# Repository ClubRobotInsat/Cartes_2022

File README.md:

# Cartes 2022
Toutes les cartes électroniques du Club pour l'année 2022 réalisées sur KiCAD. 

Liste des cartes dans ce répértoire:

|ID  | Description | 
|----|-------------|
|AAA | Carte de prototypage petite pour CAN Transreceiver MCP2551  | 
|AAB | Carte de prototypage grande pour CAN Transreceiver MCP2551  | 
|BAA | Carte du module de base pour toutes les STM32 v1            |
|BAC | Carte Alimentation 12V et 5V	                           |

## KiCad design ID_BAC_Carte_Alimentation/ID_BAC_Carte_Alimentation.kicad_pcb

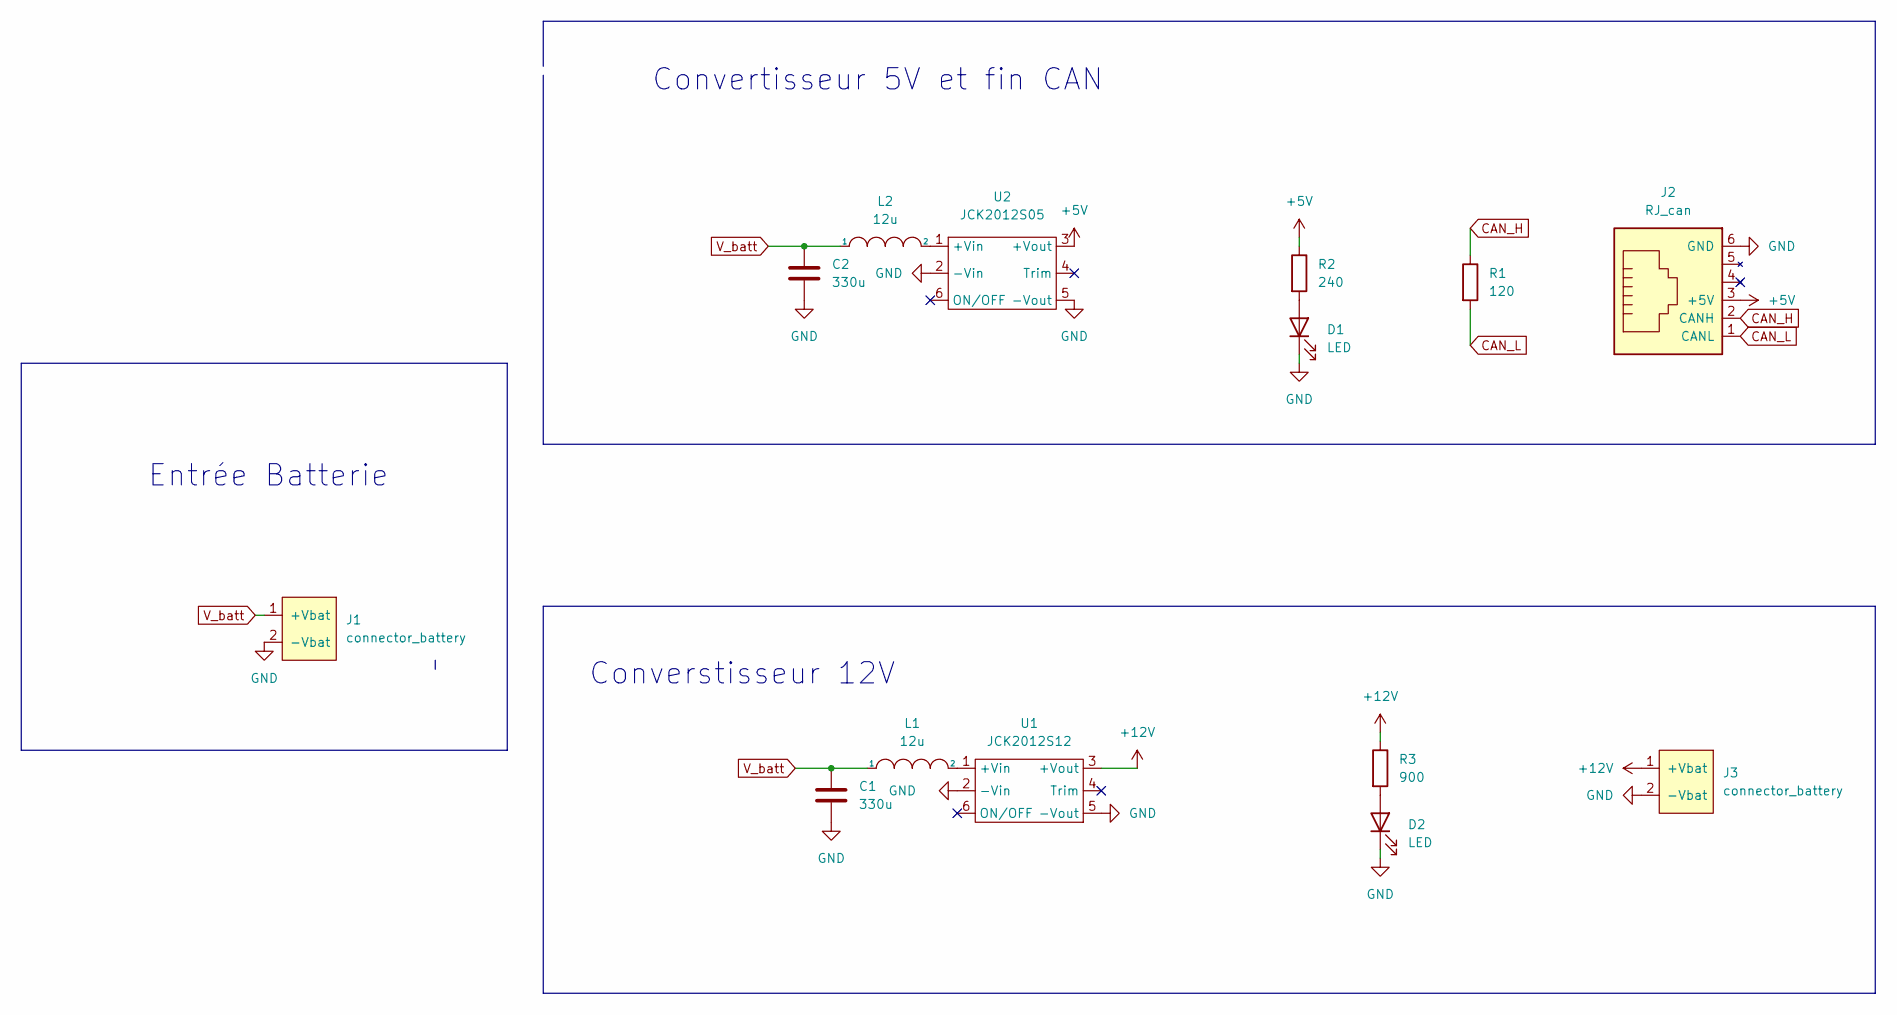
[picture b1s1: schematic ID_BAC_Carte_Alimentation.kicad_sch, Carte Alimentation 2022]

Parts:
C1, C2: 330u; CP_Radial_D7.5mm_P2.50mm
D1, D2: LED; LED_D5.0mm
J1, J3: connector_battery; WR_TBL_3137_2pins
J2: RJ_can; RJ12
L1, L2: 12u; L_Radial_D7.8mm_P5.00mm_Fastron_07HCP
R1: 120; R_0805_2012Metric_Pad1.20x1.40mm_HandSolder
R2: 240; R_0805_2012Metric_Pad1.20x1.40mm_HandSolder
R3: 900; R_0805_2012Metric_Pad1.20x1.40mm_HandSolder
U1: JCK2012S12; JCK2012S05
U2: JCK2012S05

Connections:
+5V: J2.3 (+5V), R2.1, U2.3 (+Vout)
+12V: J3.1 (+Vbat), R3.1, U1.3 (+Vout)
CAN_H: J2.2 (CANH), R1.1
CAN_L: J2.1 (CANL), R1.2
GND: C1.2, C2.2, D1.1 (K), D2.1 (K), J1.2 (-Vbat), J2.6 (GND), J3.2 (-Vbat), U1.2 (-Vin), U1.5 (-Vout), U2.2 (-Vin), U2.5 (-Vout)
unnamed: D1.2 (A), R2.2
unnamed: D2.2 (A), R3.2
unnamed: L1.2, U1.1 (+Vin)
unnamed: L2.2, U2.1 (+Vin)
V_batt: C1.1, C2.1, J1.1 (+Vbat), L1.1, L2.1

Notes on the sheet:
Entrée Batterie
Convertisseur 5V et fin CAN
Converstisseur 12V

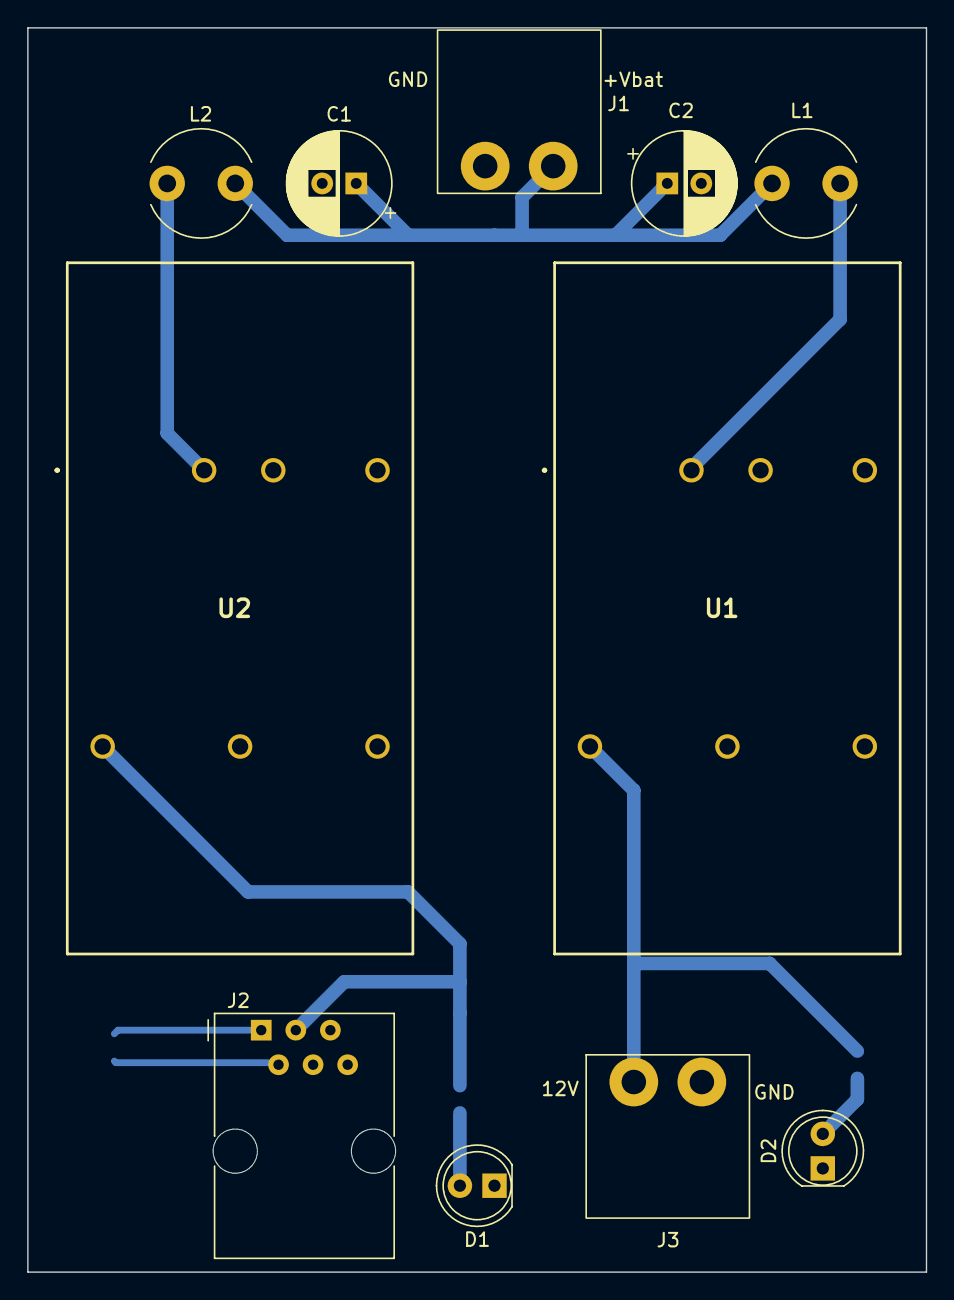
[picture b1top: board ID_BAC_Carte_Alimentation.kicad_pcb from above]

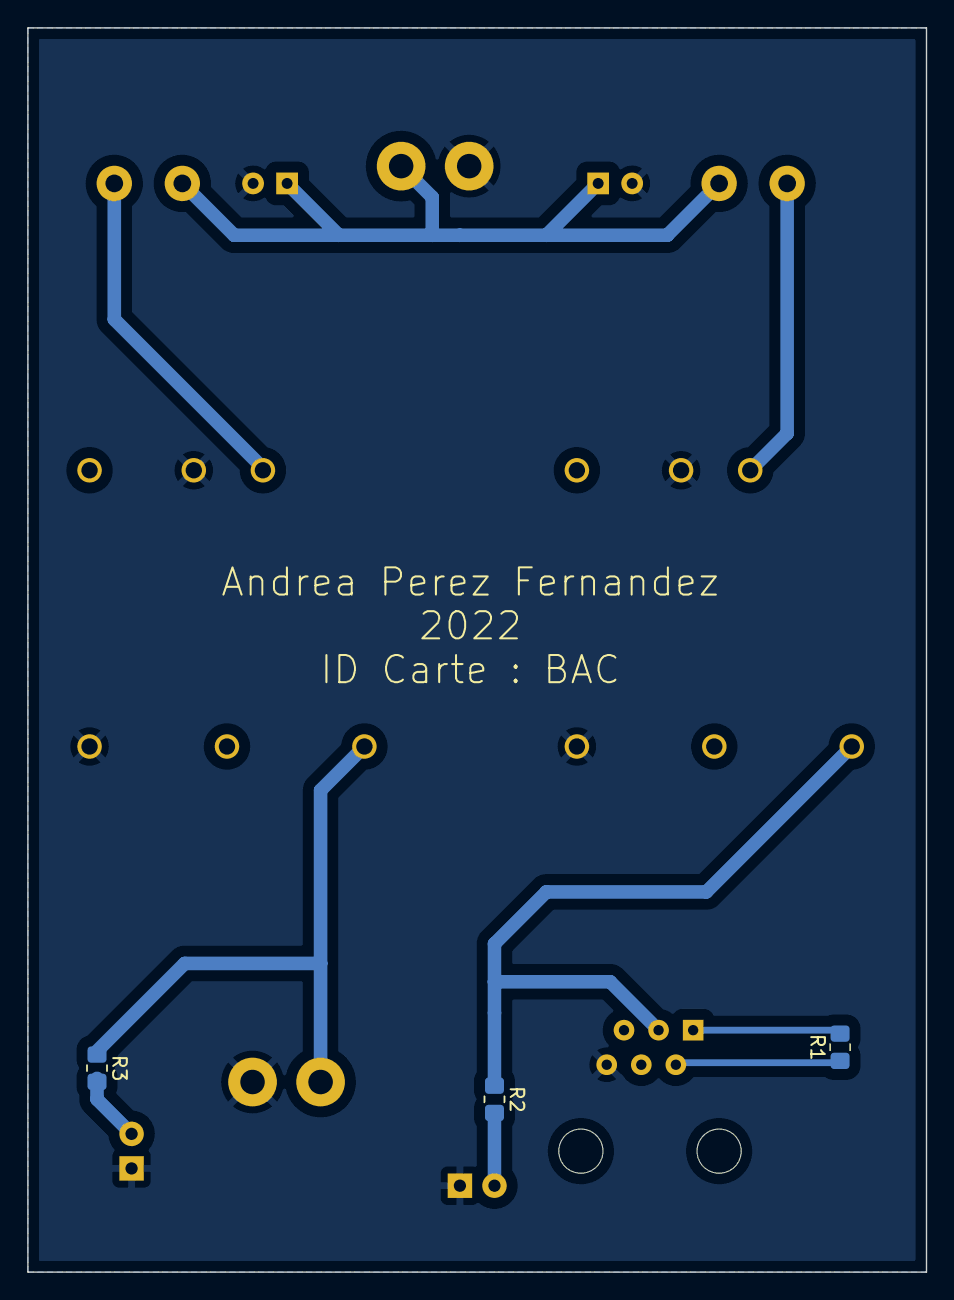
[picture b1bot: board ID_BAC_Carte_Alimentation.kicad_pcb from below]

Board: 2 copper layers, 66.0 x 91.4 mm, 14 parts (3 on the bottom side), 10 nets.

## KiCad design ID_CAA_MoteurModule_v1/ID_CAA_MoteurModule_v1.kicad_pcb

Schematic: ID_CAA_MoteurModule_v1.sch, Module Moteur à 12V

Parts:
C1: C; CP_Radial_D5.0mm_P2.00mm
J1, J2: RJ12; RJ12_Amphenol_54601
J3, J4, J7: Conn_01x02_Female; PinHeader_1x02_P2.54mm_Vertical
J5: Connecteur sortie Gauche; PinSocket_1x20_P2.54mm_Vertical
J6: Connecteur sortie Droit; PinSocket_1x20_P2.54mm_Vertical
L1: INDUCTOR; L_Axial_L7.0mm_D3.3mm_P12.70mm_Horizontal_Fastron_MICC
P1: JCK2012S12

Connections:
+5V: J5.18
+12V: J1.4, J2.4, P1.3
/DIRG: J2.1, J5.5
/DIR_D: J1.1, J6.5
/PA2: J6.14
/PA3: J6.13
/PA4: J6.12
/PA5: J6.11
/PA6: J6.10
/PA7: J6.9
/PA9: J5.6
/PA10: J5.7
/PA15: J5.10
/PB0: J6.8
/PB1: J6.7
/PB3: J5.11
/PB8: J5.16
/PB9: J5.17
/PB10: J6.6
/PB15: J5.4
/PC14: J6.18
/PC15: J6.17
/PWM_D: J1.2, J5.13
/PWM_G: J2.2, J5.12
/RC_1D: J4.1, J6.16
/RC_1G: J3.1, J5.14
/RC_2D: J4.2, J6.15
/RC_2G: J3.2, J5.15
/Valim: C1.1, J7.1, L1.1
GND: C1.2, J1.3, J2.3, J5.8, J5.9, J5.19, J6.1, J6.2, J7.2, P1.2, P1.5
unnamed: L1.2, P1.1

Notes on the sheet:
Doc pour le 3.3 -> 5 https://www.hobbytronics.co.uk/mosfet-voltage-level-converter
Connexion de Sortie
+3.3V
GND
+5V
A15
A12
A11
A10
B15
B14
B13
B12
VBT
C13
C14
C15
B10
B11
RST
Led control STM32
Convertisseur 15VDC-12VDC
Sorties RJ12 et roue codeuses
Roue Droite
Roue Gauche

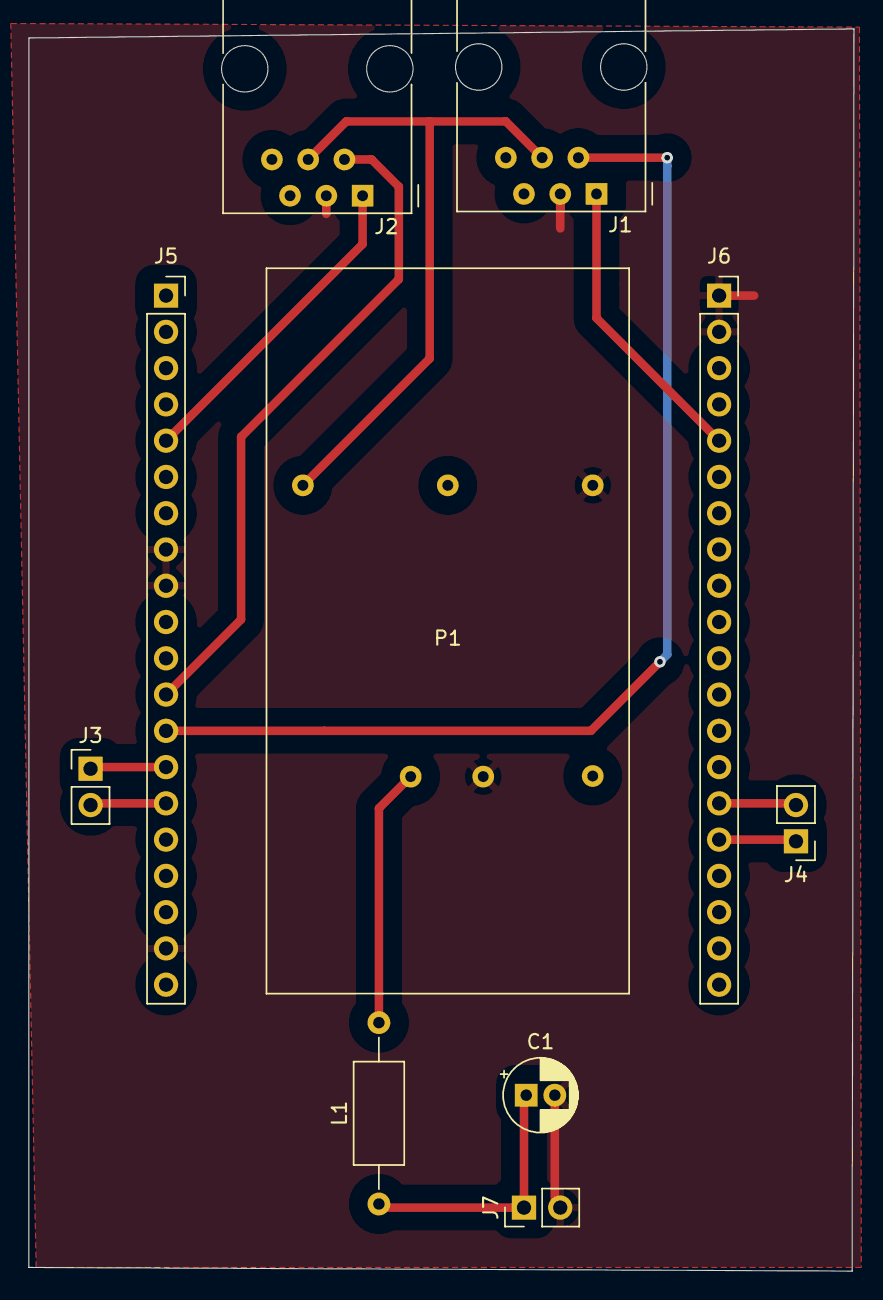
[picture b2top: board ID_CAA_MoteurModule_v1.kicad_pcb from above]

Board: 2 copper layers, 57.8 x 87.0 mm, 10 parts (0 on the bottom side), 12 nets.

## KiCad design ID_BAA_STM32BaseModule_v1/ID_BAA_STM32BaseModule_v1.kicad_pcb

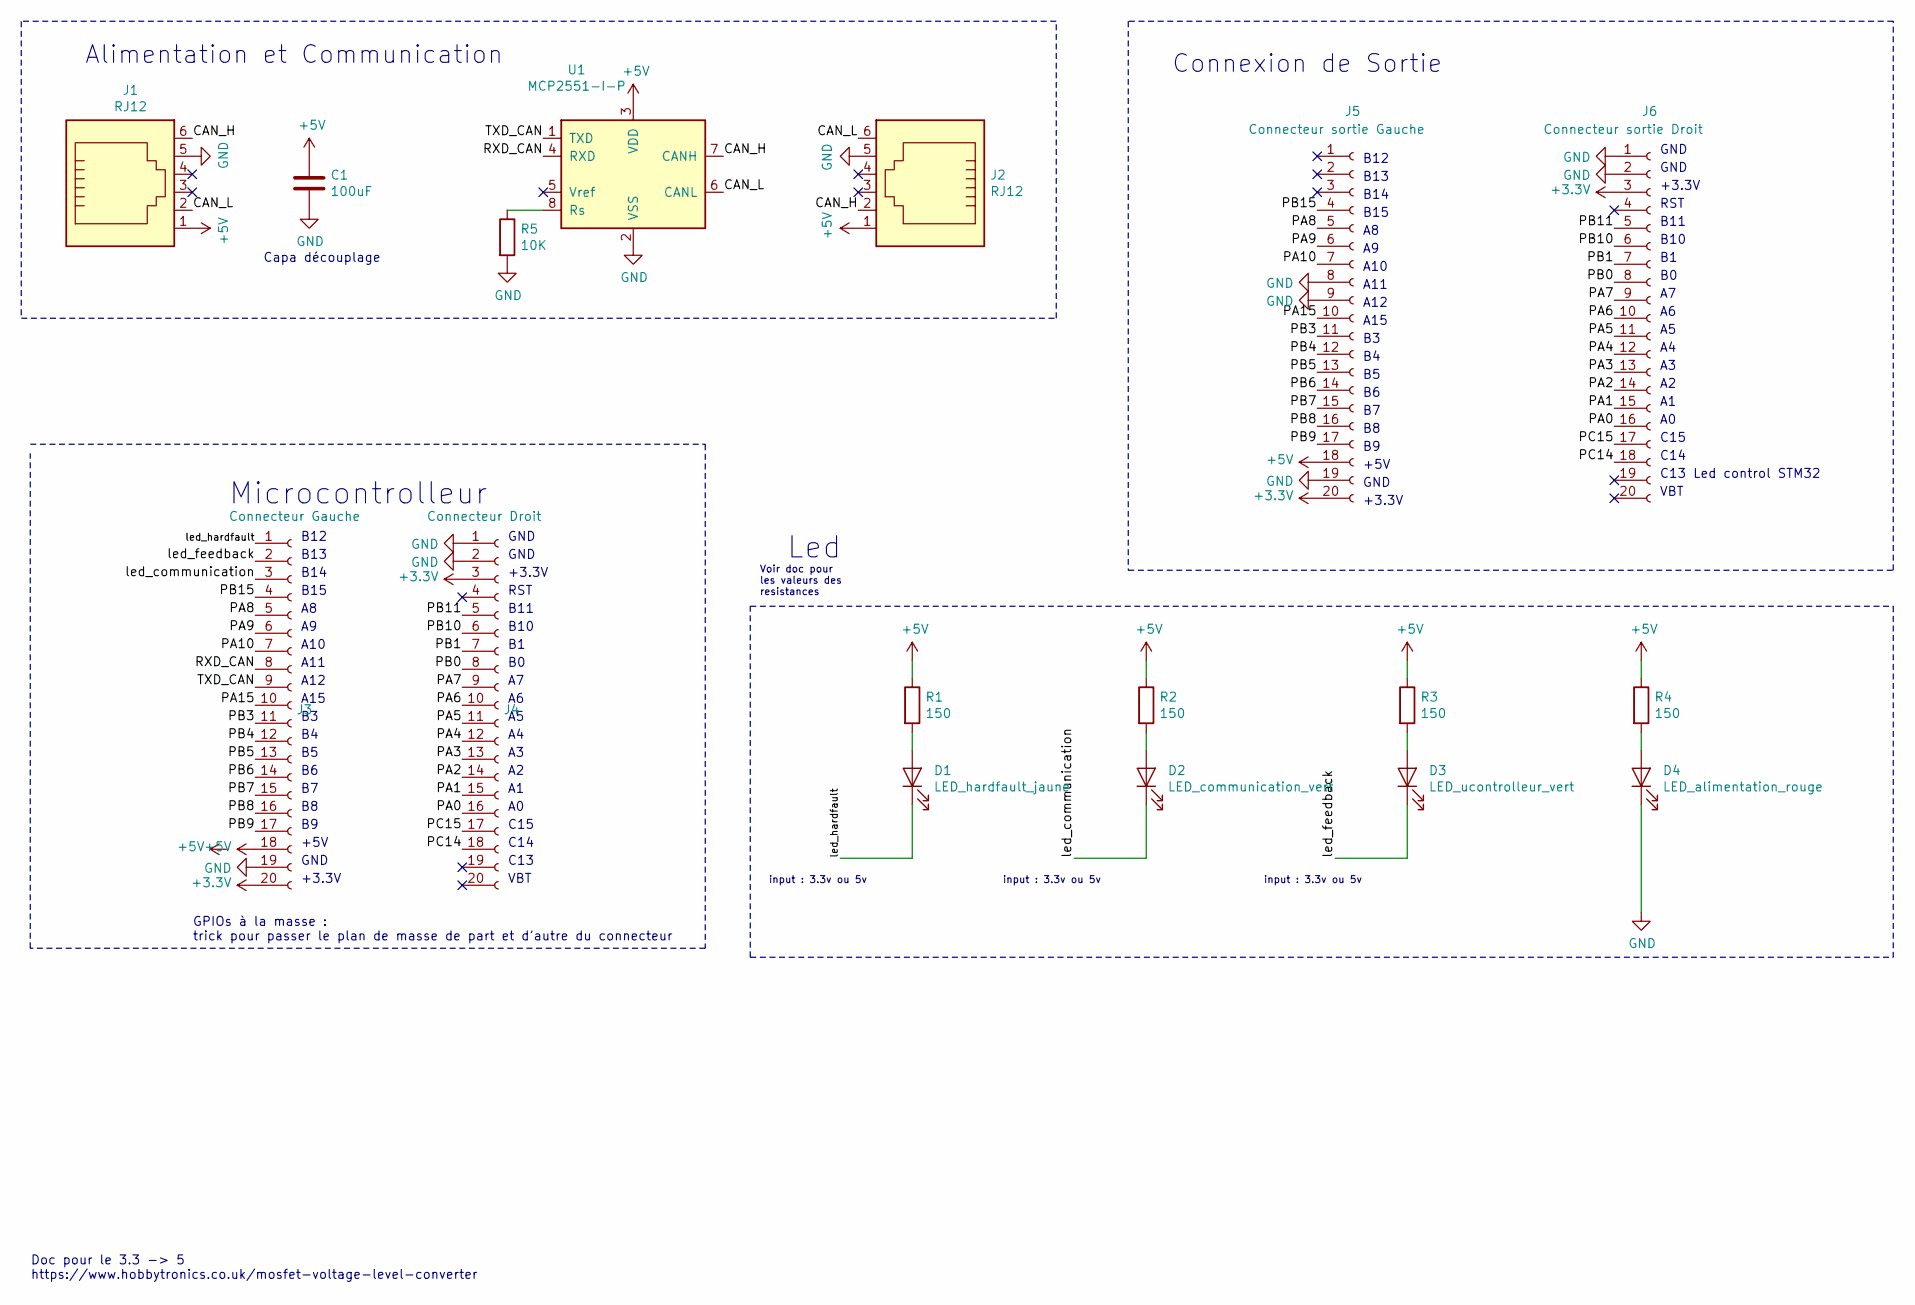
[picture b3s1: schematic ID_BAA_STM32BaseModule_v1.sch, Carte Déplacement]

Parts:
C1: 100uF; CP_Radial_D5.0mm_P2.00mm
D1: LED_hardfault_jaune; LED_D3.0mm
D2: LED_communication_vert; LED_D3.0mm
D3: LED_ucontrolleur_vert; LED_D3.0mm
D4: LED_alimentation_rouge; LED_D3.0mm
J1, J2: RJ12; RJ12_Amphenol_54601
J3: Connecteur Gauche; PinSocket_1x20_P2.54mm_Vertical
J4: Connecteur Droit; PinSocket_1x20_P2.54mm_Vertical
J5: Connecteur sortie Gauche; PinSocket_1x20_P2.54mm_Vertical
J6: Connecteur sortie Droit; PinSocket_1x20_P2.54mm_Vertical
R1: 150; R_0805_2012Metric_Pad1.15x1.40mm_HandSolder
R2, R3, R4: 150; R_0805_2012Metric
R5: 10K; R_0805_2012Metric
U1: MCP2551-I-P; SOIC-8_3.9x4.9mm_P1.27mm

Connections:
+3V3: J3.20, J4.3, J5.20, J6.3
+5V: C1.1, J1.1, J2.1, J3.18, J5.18, R1.1, R2.1, R3.1, R4.1, U1.3 (VDD)
/CAN_H: J1.6, J2.2, U1.7 (CANH)
/CAN_L: J1.2, J2.6, U1.6 (CANL)
/PA0: J4.16, J6.16
/PA1: J4.15, J6.15
/PA2: J4.14, J6.14
/PA3: J4.13, J6.13
/PA4: J4.12, J6.12
/PA5: J4.11, J6.11
/PA6: J4.10, J6.10
/PA7: J4.9, J6.9
/PA8: J3.5, J5.5
/PA9: J3.6, J5.6
/PA10: J3.7, J5.7
/PA15: J3.10, J5.10
/PB0: J4.8, J6.8
/PB1: J4.7, J6.7
/PB3: J3.11, J5.11
/PB4: J3.12, J5.12
/PB5: J3.13, J5.13
/PB6: J3.14, J5.14
/PB7: J3.15, J5.15
/PB8: J3.16, J5.16
/PB9: J3.17, J5.17
/PB10: J4.6, J6.6
/PB11: J4.5, J6.5
/PB15: J3.4, J5.4
/PC14: J4.18, J6.18
/PC15: J4.17, J6.17
/RXD_CAN: J3.8, U1.4 (RXD)
/TXD_CAN: J3.9, U1.1 (TXD)
/led_communication: D2.1 (K), J3.3
/led_feedback: D3.1 (K), J3.2
/led_hardfault: D1.1 (K), J3.1
GND: C1.2, D4.1 (K), J1.5, J2.5, J3.19, J4.1, J4.2, J5.8, J5.9, J5.19, J6.1, J6.2, R5.2, U1.2 (VSS)
unnamed: D1.2 (A), R1.2
unnamed: D2.2 (A), R2.2
unnamed: D3.2 (A), R3.2
unnamed: D4.2 (A), R4.2
unnamed: R5.1, U1.8 (Rs)

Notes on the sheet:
Led
input : 3.3v ou 5v
Microcontrolleur
Voir doc pour les valeurs des resistances
Doc pour le 3.3 -> 5 https://www.hobbytronics.co.uk/mosfet-voltage-level-converter
VBT
C13
C14
C15
B10
B11
RST
+3.3V
GND
+5V
A15
A12
A11
A10
B15
B14
B13
B12
GPIOs à la masse : trick pour passer le plan de masse de part et d’autre du connecteur
Alimentation et Communication
Capa découplage
Connexion de Sortie
Led control STM32

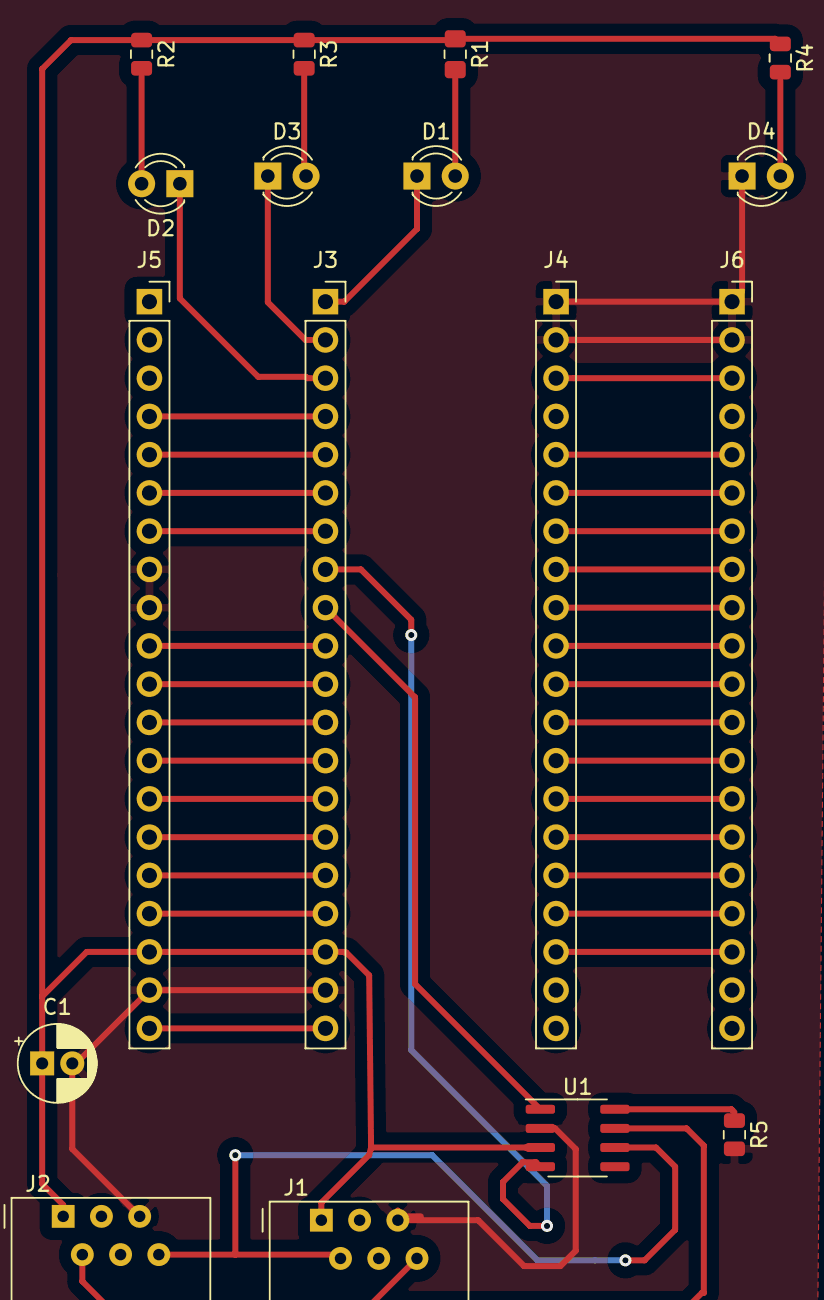
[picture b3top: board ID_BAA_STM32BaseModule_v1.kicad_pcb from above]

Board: 2 copper layers, 17 parts (0 on the bottom side), 41 nets.

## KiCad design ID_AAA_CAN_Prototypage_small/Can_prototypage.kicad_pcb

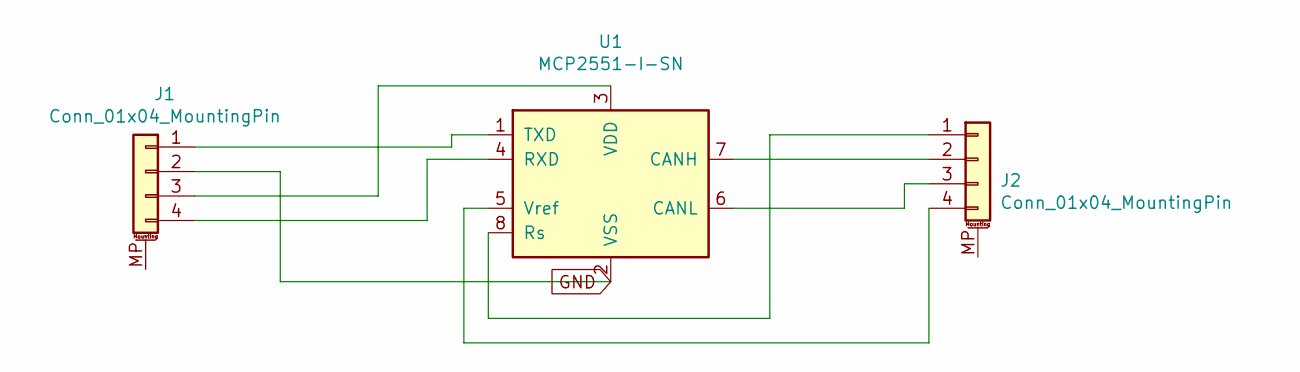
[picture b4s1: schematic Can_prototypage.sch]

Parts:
J1, J2: Conn_01x04_MountingPin; PinSocket_1x04_P2.54mm_Vertical
U1: MCP2551-I-SN; SOIC-8_3.9x4.9mm_P1.27mm

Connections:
GND: J1.2, U1.2 (VSS)
unnamed: J1.1, U1.1 (TXD)
unnamed: J1.3, U1.3 (VDD)
unnamed: J1.4, U1.4 (RXD)
unnamed: J2.1, U1.8 (Rs)
unnamed: J2.2, U1.7 (CANH)
unnamed: J2.3, U1.6 (CANL)
unnamed: J2.4, U1.5 (Vref)

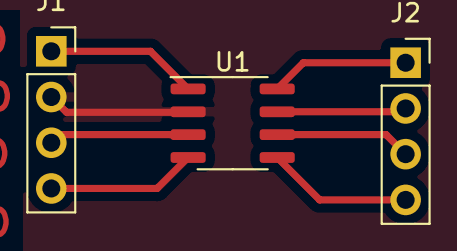
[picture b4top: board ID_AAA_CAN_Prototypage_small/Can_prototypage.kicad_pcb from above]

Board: 2 copper layers, 3 parts (0 on the bottom side), 8 nets.

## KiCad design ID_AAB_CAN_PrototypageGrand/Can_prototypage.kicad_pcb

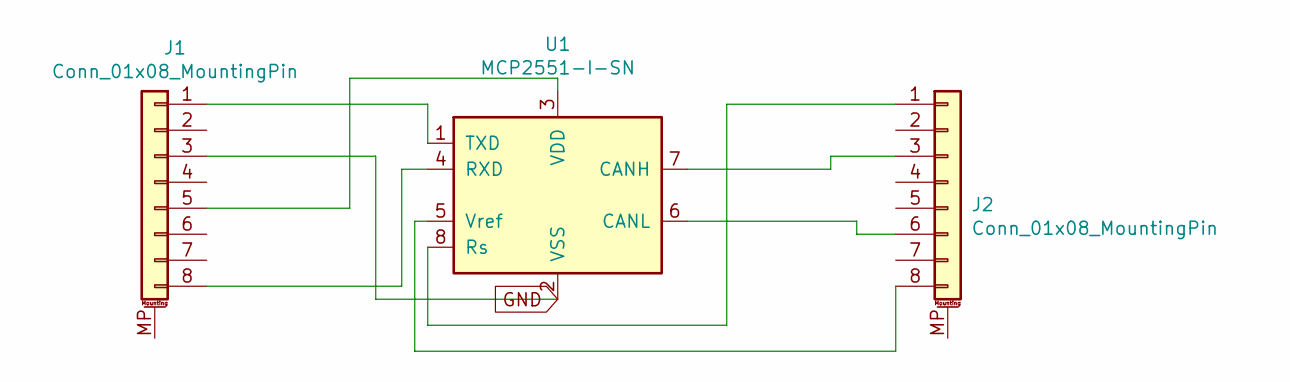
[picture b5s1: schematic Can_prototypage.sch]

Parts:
J1, J2: Conn_01x08_MountingPin; PinHeader_1x08_P2.54mm_Vertical
U1: MCP2551-I-SN; SOIC-8_3.9x4.9mm_P1.27mm

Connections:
GND: J1.3, U1.2 (VSS)
unnamed: J1.1, U1.1 (TXD)
unnamed: J1.5, U1.3 (VDD)
unnamed: J1.8, U1.4 (RXD)
unnamed: J2.1, U1.8 (Rs)
unnamed: J2.3, U1.7 (CANH)
unnamed: J2.6, U1.6 (CANL)
unnamed: J2.8, U1.5 (Vref)

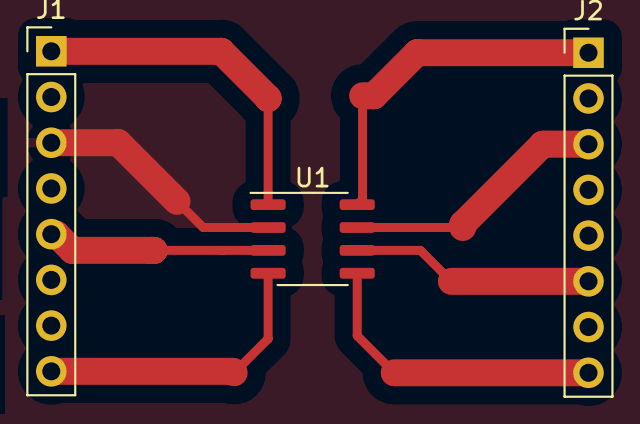
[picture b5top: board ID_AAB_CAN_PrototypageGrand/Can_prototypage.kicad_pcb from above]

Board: 2 copper layers, 3 parts (0 on the bottom side), 8 nets.

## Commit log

2022-02-08 Added AAA and AAB
    Can prototypage petit et grand
2022-02-08 LIste cartes
2022-04-02 Added STM_BaseModule
2022-04-02 add STM32_BaseModule
2022-04-02 Increase margins
2022-05-13 Modif BAA
2022-05-14 ID_CAA
2022-07-04 Carte_alim
2022-07-04 Carte_alim serigraphy
2022-07-04 gerber_files
